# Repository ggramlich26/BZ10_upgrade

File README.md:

# Bezzera BZ10 Upgrade
This Project is a replacement for the original Bezzera BZ10 electronics bringing many new features including the following:
- Temperature regulation for boiler and brewing unit
- Volumetric brewing system based on water flow instead of time only
- Standby functionality
- Automated wake up from standby, so that the machine is heated up already when you get up in the morning
- Display of various temperatures, volume distributed and distribution time
- Preinfusion (time based)
- WIFI: All parameters (temperatures, distribution volume, wake up time, etc.) can be set with a smartphone or computer
- Automated cleaning cycle: Ten cycles of switching distribution on and off for 20 seconds each by pressing only one button

## Building the project
This project is set up to be built with Eclipse Sloeber, which adds Arduino support to the Eclipse IDE. It uses the following Libraries, which can be installed through the library manager:
- TFT_eSPI (Version 1.4.16)
- Time (Version 1.5.0)
- MCP23017 (Version	1.1.2), not Adafruit MCP23017!
- PID (Version 1.2.0)
- ADS115_WE (Version 1.3.6)
- ArduinoJson (Version 6.19.4)
- ESPmDNS
- SPIFFS

Some libraries are also added as source code. If you use the Arduino IDE, please move all files from the libraries/library name/src/ directly into your project directory. If you use Sloeber, you might have to add the library paths in the project settings: Right click your project/Properties/"C/C++ Build"/Settings. In the Tool Settings Tab, expand the compiler and click Include Folders. Add the following paths ```"${workspace_loc:/BZ10_upgrade/libraries/AsyncTCP/src}"``` and ```"${workspace_loc:/BZ10_upgrade/libraries/ESPAsyncWebServer/src}"``` under each of the three compilers.

**Board settings:** You need to [install the ESP32 board for Sloeber](http://wiki.lauerbach.de/wiki/view.do?page=ESP32Entwicklungsumgebungen). Select NodeMCU-32S as board, Upload Protocol: Default, Flash Frequency: 40MHz, Upload Speed: 115200

***Windows:*** Under windows you need to make sure you have make command installed (e.g. through MinGW64: select mingw32-make package). You might also have to [install CP2102 drivers](https://www.silabs.com/developers/usb-to-uart-bridge-vcp-drivers) if you get a timeout error when trying to upload your sketch.

**Before building** 
You will additionally need to modify User_Setup.h in the TFT_eSPI library folder. Uncomment `#define ILI9341_DRIVER` (line 39) and make sure all other lines in this block are commented out. Then search for the uncommented pin definitions and change them to the following:
```C++
#define TFT_DC 		23
#define TFT_CS 		17
#define	TFT_MOSI	32
#define	TFT_SCLK	33
#define	TFT_MISO	14
#define TFT_RST		16
```

## Setting your WiFi credentials
The machine can be configured to connect to your own home WiFi network via the web interface:
 1. Turn the machine off.
 2. Set the brewing switch to manual mode, hold both buttons pressed (This step resets the wifi configuration. You can omit it if you have a fresh setup).
 3. Turn the machine on while holding the buttons pressed. You can release them once the screen is ready.
 4. Wait for 30 seconds
 5. Connect with any device to the WiFi network "BZ10" with no password required.
 6. Open your web browser and type 192.168.4.1 into address bar, hit enter.
 7. Now you will be presented a prompt to enter the new SSID (your WiFi name) and password. You can also set your machines Bonjour name. Finish by hitting the "Set" button.

## Connecting to the machine
You can connect to the machine with a browser on any device. You can use your computer, smartphone or tablet, for example. Please note: The machine currently **only supports http and not https**. If you cannot connect, you might have to change the line ine your browser to http://your-ip. There are multiple ways to connect:
### Access point mode
When the machine cannot establish a connection to a wifi network, it automatically creates a hotspot after 30 seconds. Simply connect to the network BZ10 with your device. In the browser type in 192.168.4.1 to go to your machine and change the settings.
### Local WiFi
If the machine is connected to your local WiFi network (little wifi icon shown in the bottom), you can reach it by typing its IP in your browser (use your router configuration website to find out what that is and to make it always the same). Alternatively, you can find it with Bonjour. This works out of the box on Apple and Linux machines and requires an extra [installation from the apple resources](https://support.apple.com/downloads/bonjour-for-windows) on windows. You can then reach the machine by typing bz10.local into your browser. If you want to change the address to something else than bz10, you can modify the Bonjour name on the machine website.
## Usage
Your new espresso machine has a lot more functions than before. This is how you can use them
- **Standard manual distribution:** Flip your distribution switch in the manual distribution position for manual dosing and cooling flush
- **True volumetric distribution:** Flip your distribution switch in the volumetric distribution position for automatic dosing. You can set the desired volume via the website. You will also need to set an offset volume that compensates for the water being moved into the brewing unit but not going through your coffee powder. The best way to do so is to measure the difference between set and actual distribution volume and entering this value via Blynk.
- **Preinfusion:** If you set a preinfusion buildup and wait time on the website, volumetric distribution will come with a preinfusion. This is achieved by turning on the pump for the preinfusion buildup time and then waiting for the preinfusion wait time before starting the actual extraction.
- **Cooling flush:** Since the BZ10 is a HX machine, you will still need to perform a cooling flush just like before the upgrade. But in order to make this process more repeatable, you get a timer showing the time passed after your cooling flush. In order to get this functionality, short press the right button before starting your cooling flush. You will see, that the timer starts counting up once you finished your cooling flush.
- **Standby:** Press the left button shortly to enter standby mode. You can also define a period of time after which the machine will automatically enter standby if it has not been used via Blynk.
- **Automated wake up from standby:** Tired of having to wait for half an hour after getting up until you can finally brew your coffee? Just turn your espresso machine on and press the standby button before going to bed. Now you can set a wake up time via the website. If you set it to half an hour before your alarm goes off, your machine will be all ready for your coffee first thing in the morning. This feature only works if wifi is enabled and the machine has connection to the internet, since it needs to get the current time from a remote server.
- **Automated cleaning cycle:** Cleaning is boring and time consuming task. But now you can save a lot of time. Pressing the right button for 3s or more will start an automated cleaning cycle: Your machine will build up pressure for 20s and then release it for another 20s. This process is repeated 10 times.
- **Disable WiFi:** You got everything set up and don't want your machine to be in the internet any more? Nothing easier than that. Just press the left button for 3s or longer. Now you can see the wifi symbol disappearing from the display and once you restart your machine it won't even connect to your WiFi network any more. To enable WiFi again, just press the left button for 3s or longer again. 
- **Display:** Pretty obvious but you now have a display showing various temperatures, the volume distributed and the time your distribution took (preinfusion time not included). The red circle shows the boiler temperature, the orange circle on the right shows the brewing head temperature and the blue circle in the top shows one additional temperature. I attached this sensor to the tube leading from the heat exchanger to the brewing head.

## Code overview
The machine functionality is based on state machines. There are two state machines for boiler and brewing unit temperature control. Another state machine controls the brewing cycle, one is used for the display, and a last one is responsible for the overall machine state including standby functionality. All state machines are visually shown under `/State machines/State machines.odg`. 
In order to make the program more flexible for other hardware, a hardware abstraction class has been written (`dev.c`). Adapting this class will allow the project to run on a different hardware as well.
Besides machine logic, a faster library for TSIC temperature sensors has been developed.
### Brewing state machine
### Boiler heater state machine
### Brewing unit heater state machine
### Display state machine
### Machine status state machine

## The Hardware
There are eagle layout and gerber files available for a PCB designed with this project. You can simply send those files to a manufacturer such as JLCPCB or Seeedstudio. At the moment I also have a few available from my order, that I could have sent to you for very little money. In case you have trouble soldering SMD (surface mounted device) components, we could also discuss having an assembled PCB shipped to you.
### Hardware on the PCB
You will need all need the components listed below to complete the PCB. All of them can be bought from standard suppliers, including Reichelt, Farnell, Mouser etc.

**Resistors:**
|Value|Package | Quantity | Link |
|--|--|--|--
|2.2k|0603|1
|4.7k|0603|2
|10k|0603|2
|22k|0603|3
|47k|0603|2
|100k|0603|1
220k|0603|2
330k|0603|3
1M|0603|1
4.7M|0603|1

**Capacitors:**
|Value|Package | Quantity | Link |
|--|--|--|--
2.2n|0603|1
10n|0603|2
22n|0603|1
100n|0603|2

**Semiconductors:**
|Name|Package | Quantity | Link |
|--|--|--|--
| **Transistors**|
 IRLML5203|MICRO3|1|[farnell](https://de.farnell.com/infineon/irlml5203trpbf/mosfet-p-kanal-30v-3a-sot23/dp/9103511?st=irlml5203)
 BSS138BK|SOT-23|6|[farnell](https://de.farnell.com/nexperia/bss138bk-215/mosfet-n-kanal-60v-0-36a-sot23/dp/2053833?st=bss138bk)
 **Diodes**|
 BAS21|SOT-23|2|[farnell](https://de.farnell.com/diodes-inc/bas21/schaltdiode-250v-0-25w-sot23-3/dp/1902406?st=bas21)
 **ICs**|
 MCP23017SO|SO28W|1|[farnell](https://de.farnell.com/microchip/mcp23017-e-so/16bit-expander-i-o-i2c-i-f-smd/dp/1332087?st=mcp23017)
 NE555D|SO-8|1|[farnell](https://de.farnell.com/texas-instruments/ne555d/precision-timers-linear/dp/3121191?st=ne555d)
 MCP6002-E/SN|SOIC-8|1|[farnell](https://de.farnell.com/microchip/mcp6002-e-sn/op-verst-rker-1mhz-0-6v-us-4500uv/dp/1332118?st=mcp6002-e/sn)
  ADS1115|MSOP10|1|[e.g. from far east](https://www.aliexpress.com/item/32809831068.html?spm=a2g0s.9042311.0.0.27424c4daHnzqu)

**Boards:**
|Name|Package | Quantity | Link |
|--|--|--|--
| ESP32 nodeMCU with external antenna||1|[from far east](https://www.aliexpress.com/item/4000155919030.html?spm=a2g0s.9042311.0.0.27424c4d4ySog2)|

**Power supply:**
|Name|Package | Quantity | Link |
|--|--|--|--
| HLK-PM01 (5V power supply)||1|[from far east](https://www.aliexpress.com/item/4000534910455.html?spm=a2g0s.9042311.0.0.2f024c4dAwDw9T)|

**Connectors:**
|Name|rows|positions|m/f| Quantity | Comment |
|--|--|--|--|--|--
pinheader 2.54mm|1|2|f+m|4|boiler SSR, boiler probe, NTC, tank switch
pinheader 2.54mm|1|3|f+m|5|connecting TSIC temperature and flow sensors
pinheader 2.54mm|1|6|f+m|2|connecting arduino SSR board
pinheader 2.54mm|1|8|f+m|2|connecting switches and LEDs
pinheader 2.54mm|1|9|f+m|2|display
wire to board connectors, RM5 with screws|1|2|f|1|230V connector [farnell](https://de.farnell.com/camdenboss/ctb1500-2/terminal-block-5mm-2-way/dp/3377326?st=wire%20to%20board%20rm5)

### Hardware off the PCB in the machine
- Arduino SSR board with 4 SSRs (e.g. [Arduino SSR module on Amazon](https://www.amazon.de/Ecloud-4-Channel-Trigger-SSR-Modul-Brett-Arduino-resistivem/dp/B01E6KUMTI/ref=sr_1_4?__mk_de_DE=%C3%85M%C3%85%C5%BD%C3%95%C3%91&dchild=1&keywords=arduino%20ssr%204&qid=1605773053&quartzVehicle=812-409&replacementKeywords=arduino%20ssr&sr=8-4))
- One SSRs for 230V, switchable by 3-5VDC (called SSR-40 DA) for boiler heater and electric brewing unit heater (e.g. [SSR on Amazon](https://www.amazon.de/KKmoon-24V-380V-SSR-40-Relaismodul-Temperaturregler/dp/B010Q6898C/ref=sr_1_3?__mk_de_DE=%C3%85M%C3%85%C5%BD%C3%95%C3%91&dchild=1&keywords=ssr&qid=1605773227&sr=8-3))
- SPI TFT Display 320x240 Pixels with ILI9341 (e.g. [Display on Amazon](https://www.amazon.de/gp/product/B01E0MGZU2/ref=ppx_yo_dt_b_asin_title_o09_s00?ie=UTF8&psc=1))
- Alternative switches: Brewing switch should be replaced by a 3 fixed positions switch, indicator lights should be replaced by push buttons with LEDs, so that they can serve as indicator lights and inputs at the same time. (I used [those](https://www.aliexpress.com/item/4000454624299.html?spm=a2g0s.9042311.0.0.27424c4dZZ9bgU) instead of the indicator lights (3-6V, momentary version) and [those](https://www.aliexpress.com/item/4000028451024.html?spm=a2g0s.9042311.0.0.27424c4dZZ9bgU) for the original two push buttons (5V, latching fixation, blue LED, 2 positions for on/off, 3 positions for brewing switch). If you want to use those switches for on/off, you will need to add a relay in the power supply chain because they are not strong enough for the entire espresso machine power!
- TSIC 306 temperature sensors, 3 pieces
- Flow sensors, 2 pieces (e.g. [from far east](https://www.aliexpress.com/item/32949504762.html?spm=a2g0o.productlist.0.0.4ce346a5MgsR2I&algo_pvid=a8a64f8f-1437-4fca-a7c7-6e23d0d647a1&algo_expid=a8a64f8f-1437-4fca-a7c7-6e23d0d647a1-28&btsid=2100bdf016057823158403471e2893&ws_ab_test=searchweb0_0,searchweb201602_,searchweb201603_))
- Quite some wiring. I chose Oelflex Heat for its heat resistance up to 180°C (purchased from Conrad electronics)

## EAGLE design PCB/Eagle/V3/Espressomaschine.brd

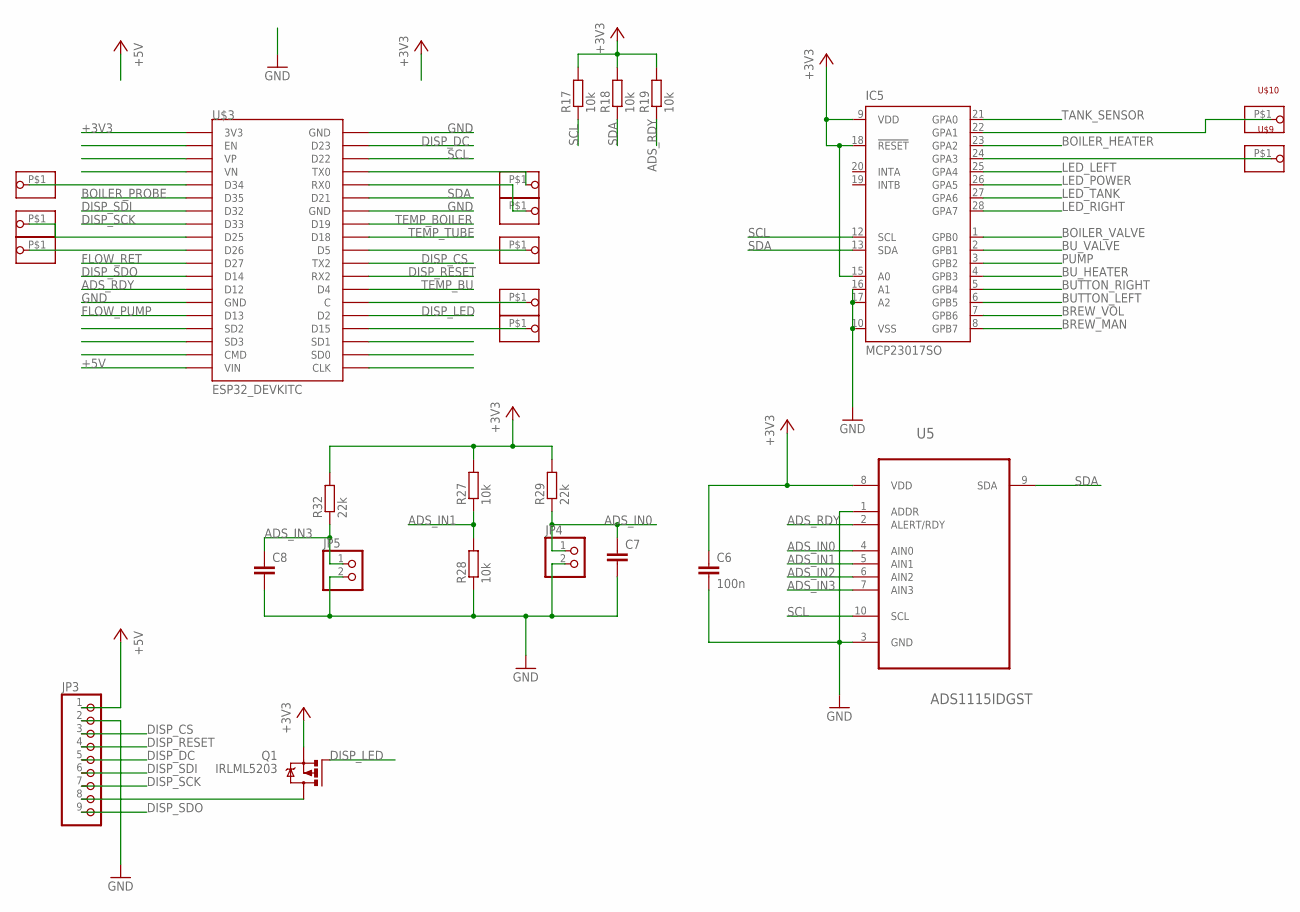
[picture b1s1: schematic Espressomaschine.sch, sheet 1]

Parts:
C6: 100n; C0603
C7, C8: C-EUC0603; C0603
IC5: MCP23017SO; SO28W
JP3: PINHD-1X9; 1X09
JP4, JP5: PINHD-1X2; 1X02
Q1: IRLML5203; MICRO3
R17, R18, R19, R27, R28: 10k; R0603
R29, R32: 22k; R0603
U5: ADS1115IDGST; SOP50P490X110-10N
U$3: ESP32_DEVKITC
U$5, U$6, U$7, U$8, U$9, U$10, U$11, U$12, U$13, U$14: PINHD-1X1SMD_RM1.27; 1X01_SMD_RM1.27

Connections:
+3V3: C6.1, IC5.9 (VDD), IC5.15 (A0), IC5.18 (!RESET), Q1.2 (S), R17.2, R18.2, R19.2, R27.2, R29.2, R32.2, U5.8 (VDD), U$3.3V3; also elsewhere on the board
+5V: JP3.1, U$3.VIN; also elsewhere on the board
ADS_IN0: C7.1, JP4.1, R29.1, U5.4 (AIN0)
ADS_IN1: R27.1, R28.2, U5.5 (AIN1)
ADS_IN2: U5.6 (AIN2); also elsewhere on the board
ADS_IN3: C8.1, JP5.1, R32.1, U5.7 (AIN3)
ADS_RDY: R19.1, U5.2 (ALERT/RDY), U$3.D12
BOILER_HEATER: IC5.23 (GPA2); also elsewhere on the board
BOILER_PROBE: U$3.D35; also elsewhere on the board
BOILER_VALVE: IC5.1 (GPB0); also elsewhere on the board
BREW_MAN: IC5.8 (GPB7); also elsewhere on the board
BREW_VOL: IC5.7 (GPB6); also elsewhere on the board
BUTTON_LEFT: IC5.6 (GPB5); also elsewhere on the board
BUTTON_RIGHT: IC5.5 (GPB4); also elsewhere on the board
BU_HEATER: IC5.4 (GPB3); also elsewhere on the board
BU_VALVE: IC5.2 (GPB1); also elsewhere on the board
DISP_CS: JP3.3, U$3.TX2
DISP_DC: JP3.5, U$3.D23
DISP_LED: Q1.1 (G), U$3.D2
DISP_RESET: JP3.4, U$3.RX2
DISP_SCK: JP3.7, U$3.D33
DISP_SDI: JP3.6, U$3.D32
DISP_SDO: JP3.9, U$3.D14
FLOW_PUMP: U$3.D13; also elsewhere on the board
FLOW_RET: U$3.D27; also elsewhere on the board
GND: C6.2, C7.2, C8.2, IC5.10 (VSS), IC5.16 (A1), IC5.17 (A2), JP3.2, JP4.2, JP5.2, R28.1, U5.1 (ADDR), U5.3 (GND), U$3.GND@1 (GND), U$3.GND@2 (GND), U$3.GND@3 (GND); also elsewhere on the board
LED_LEFT: IC5.25 (GPA4); also elsewhere on the board
LED_POWER: IC5.26 (GPA5); also elsewhere on the board
LED_RIGHT: IC5.28 (GPA7); also elsewhere on the board
LED_TANK: IC5.27 (GPA6); also elsewhere on the board
unnamed: U$3.C, U$7.P$1
unnamed: IC5.22 (GPA1), U$10.P$1
unnamed: IC5.24 (GPA3), U$9.P$1
unnamed: U$3.TX0, U$5.P$1
unnamed: JP3.8, Q1.3 (D)
unnamed: U$3.RX0, U$11.P$1
unnamed: U$3.D5, U$6.P$1
unnamed: U$3.D15, U$8.P$1
unnamed: U$3.D34, U$12.P$1
unnamed: U$3.D25, U$13.P$1
unnamed: U$3.D26, U$14.P$1
PUMP: IC5.3 (GPB2); also elsewhere on the board
SCL: IC5.12 (SCL), R17.1, U5.10 (SCL), U$3.D22
SDA: IC5.13 (SDA), R18.1, U5.9 (SDA), U$3.D21
TANK_SENSOR: IC5.21 (GPA0); also elsewhere on the board
TEMP_BOILER: U$3.D19; also elsewhere on the board
TEMP_BU: U$3.D4; also elsewhere on the board
TEMP_TUBE: U$3.D18; also elsewhere on the board

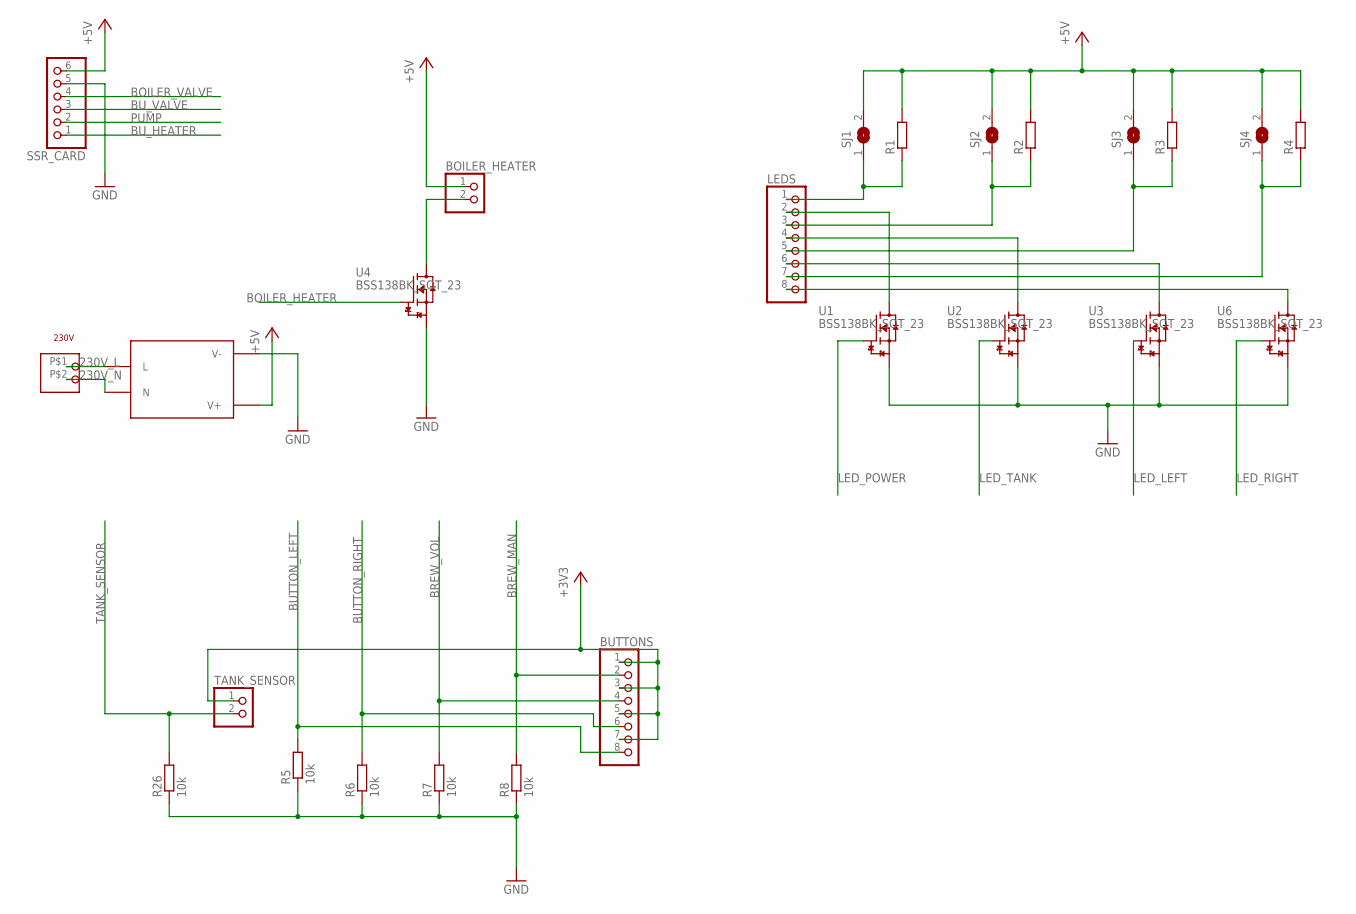
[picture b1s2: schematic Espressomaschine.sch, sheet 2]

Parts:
230V: 1X2RM5; 1X02_RM5
BOILER_HEATER: PINHD-1X2; 1X02
BUTTONS: PINHD-1X8; 1X08
LEDS: PINHD-1X8; 1X08
R1, R2, R3, R4: R-EU_R0603; R0603
R5, R6, R7, R8, R26: 10k; R0603
SJ1, SJ2, SJ3, SJ4: SJ
SSR_CARD: PINHD-1X6; 1X06
TANK_SENSOR: PINHD-1X2; 1X02
U1, U2, U3, U4, U6: BSS138BK_SOT_23; SOT23
U$1: HLK-PM0X

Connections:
230V_L: 230V.P$1 (1), U$1.L
230V_N: 230V.P$2 (2), U$1.N
+3V3: BUTTONS.1, BUTTONS.3, BUTTONS.5, BUTTONS.7, TANK_SENSOR.1; also elsewhere on the board
+5V: BOILER_HEATER.1, R1.2, R2.2, R3.2, R4.2, SJ1.2, SJ2.2, SJ3.2, SJ4.2, SSR_CARD.6, U$1.V+; also elsewhere on the board
BOILER_HEATER: U4.1 (G); also elsewhere on the board
BOILER_VALVE: SSR_CARD.4; also elsewhere on the board
BREW_MAN: BUTTONS.2, R8.2; also elsewhere on the board
BREW_VOL: BUTTONS.4, R7.2; also elsewhere on the board
BUTTON_LEFT: BUTTONS.8, R5.2; also elsewhere on the board
BUTTON_RIGHT: BUTTONS.6, R6.2; also elsewhere on the board
BU_HEATER: SSR_CARD.1; also elsewhere on the board
BU_VALVE: SSR_CARD.3; also elsewhere on the board
GND: R5.1, R6.1, R7.1, R8.1, R26.1, SSR_CARD.5, U1.2 (S), U2.2 (S), U3.2 (S), U4.2 (S), U6.2 (S), U$1.V-; also elsewhere on the board
LED_LEFT: U3.1 (G); also elsewhere on the board
LED_POWER: U1.1 (G); also elsewhere on the board
LED_RIGHT: U6.1 (G); also elsewhere on the board
LED_TANK: U2.1 (G); also elsewhere on the board
unnamed: LEDS.1, R1.1, SJ1.1
unnamed: LEDS.3, R2.1, SJ2.1
unnamed: LEDS.5, R3.1, SJ3.1
unnamed: LEDS.8, U6.3 (D)
unnamed: LEDS.6, U3.3 (D)
unnamed: BOILER_HEATER.2, U4.3 (D)
unnamed: LEDS.7, R4.1, SJ4.1
unnamed: LEDS.4, U2.3 (D)
unnamed: LEDS.2, U1.3 (D)
PUMP: SSR_CARD.2; also elsewhere on the board
TANK_SENSOR: R26.2, TANK_SENSOR.2; also elsewhere on the board

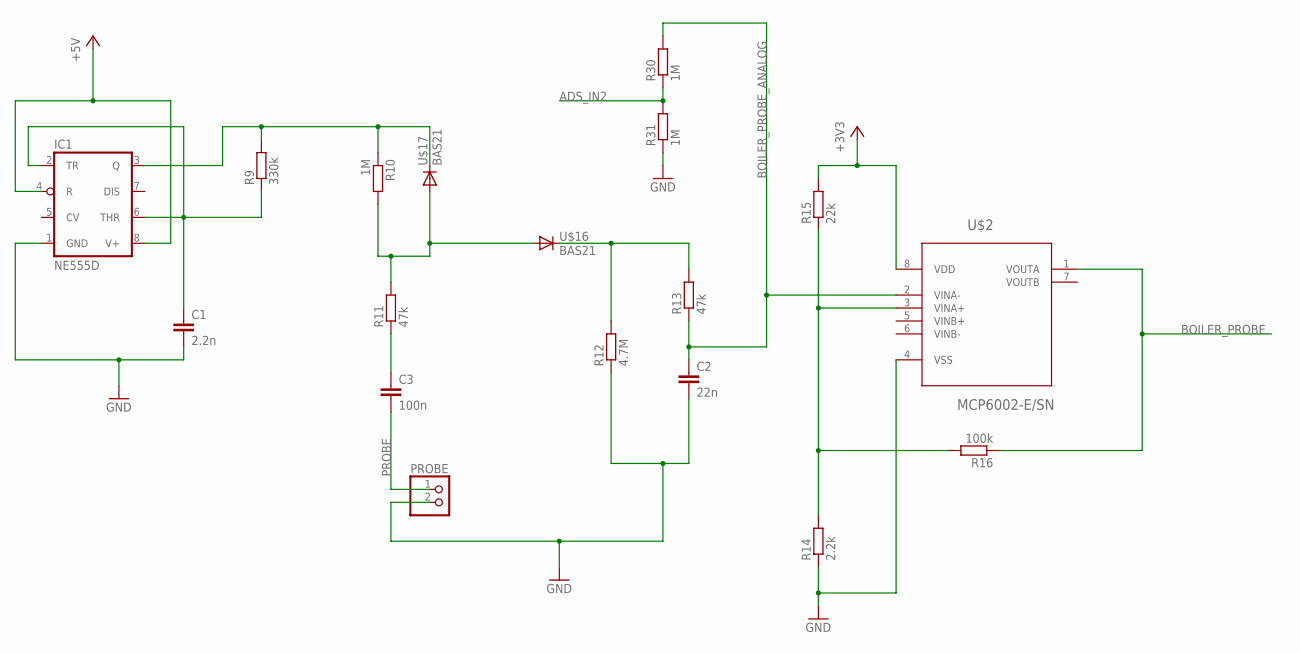
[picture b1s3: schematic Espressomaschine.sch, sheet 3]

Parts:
C1: 2.2n; C0603
C2: 22n; C0603
C3: 100n; C0603
IC1: NE555D; SO08
PROBE: PINHD-1X2; 1X02
R9: 330k; R0603
R10, R30, R31: 1M; R0603
R11, R13: 47k; R0603
R12: 4.7M; R0603
R14: 2.2k; R0603
R15: 22k; R0603
R16: 100k; R0603
U$2: MCP6002-E/SN; SOIC127P600X175-8N
U$16, U$17: BAS21; SOT23

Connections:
+3V3: R15.2, U$2.8 (VDD); also elsewhere on the board
+5V: IC1.4 (R), IC1.8 (V+); also elsewhere on the board
ADS_IN2: R30.1, R31.2; also elsewhere on the board
BOILER_PROBE: R16.1, U$2.1 (VOUTA); also elsewhere on the board
BOILER_PROBE_ANALOG: C2.1, R13.1, R30.2, U$2.2 (VINA-)
GND: C1.2, C2.2, IC1.1 (GND), PROBE.2, R12.1, R14.1, R31.1, U$2.4 (VSS); also elsewhere on the board
unnamed: C1.1, IC1.2 (TR), IC1.6 (THR), R9.1
unnamed: R10.2, R11.2, U$16.1 (A), U$17.1 (A)
unnamed: C3.1, R11.1
unnamed: IC1.3 (Q), R9.2, R10.1, U$17.3 (C)
unnamed: R12.2, R13.2, U$16.3 (C)
unnamed: R14.2, R15.1, R16.2, U$2.3 (VINA+)
PROBE: C3.2, PROBE.1

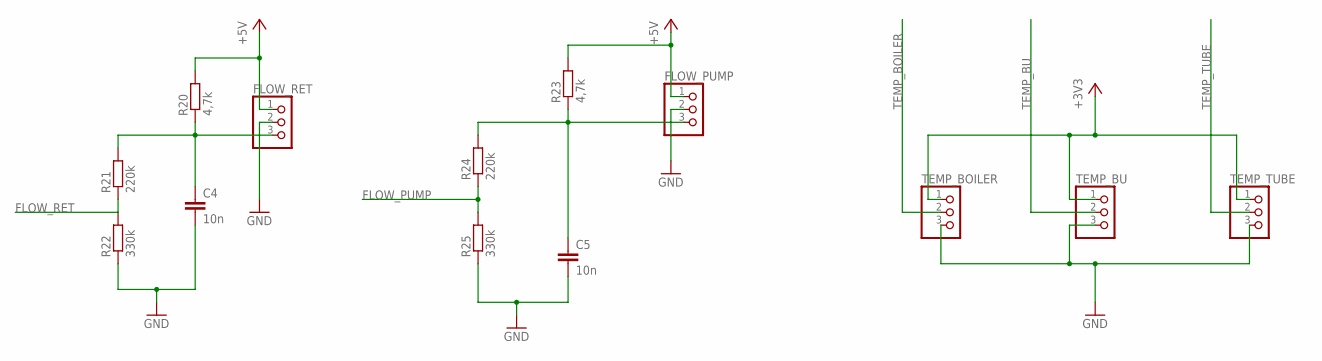
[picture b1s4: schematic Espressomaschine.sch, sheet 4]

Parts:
C4, C5: 10n; C0603
FLOW_PUMP: PINHD-1X3; 1X03
FLOW_RET: PINHD-1X3; 1X03
R20, R23: 4,7k; R0603
R21, R24: 220k; R0603
R22, R25: 330k; R0603
TEMP_BOILER: PINHD-1X3; 1X03
TEMP_BU: PINHD-1X3; 1X03
TEMP_TUBE: PINHD-1X3; 1X03

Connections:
+3V3: TEMP_BOILER.1, TEMP_BU.1, TEMP_TUBE.1; also elsewhere on the board
+5V: FLOW_PUMP.1, FLOW_RET.1, R20.2, R23.2; also elsewhere on the board
FLOW_PUMP: R24.1, R25.2; also elsewhere on the board
FLOW_RET: R21.1, R22.2; also elsewhere on the board
GND: C4.2, C5.2, FLOW_PUMP.2, FLOW_RET.2, R22.1, R25.1, TEMP_BOILER.3, TEMP_BU.3, TEMP_TUBE.3; also elsewhere on the board
unnamed: C4.1, FLOW_RET.3, R20.1, R21.2
unnamed: C5.1, FLOW_PUMP.3, R23.1, R24.2
TEMP_BOILER: TEMP_BOILER.2; also elsewhere on the board
TEMP_BU: TEMP_BU.2; also elsewhere on the board
TEMP_TUBE: TEMP_TUBE.2; also elsewhere on the board

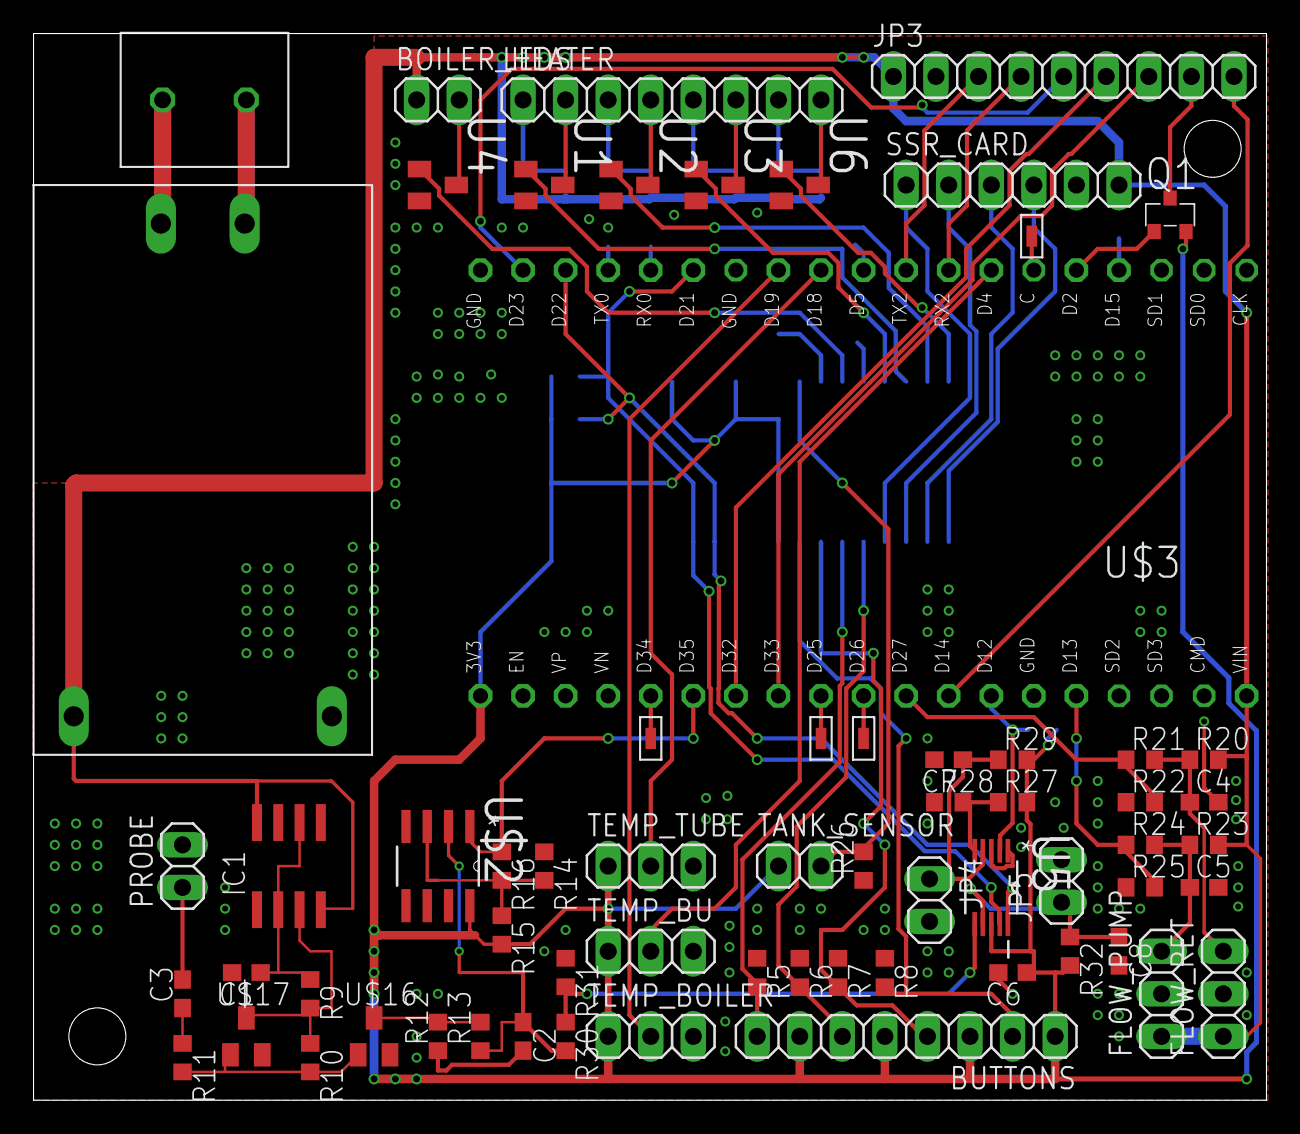
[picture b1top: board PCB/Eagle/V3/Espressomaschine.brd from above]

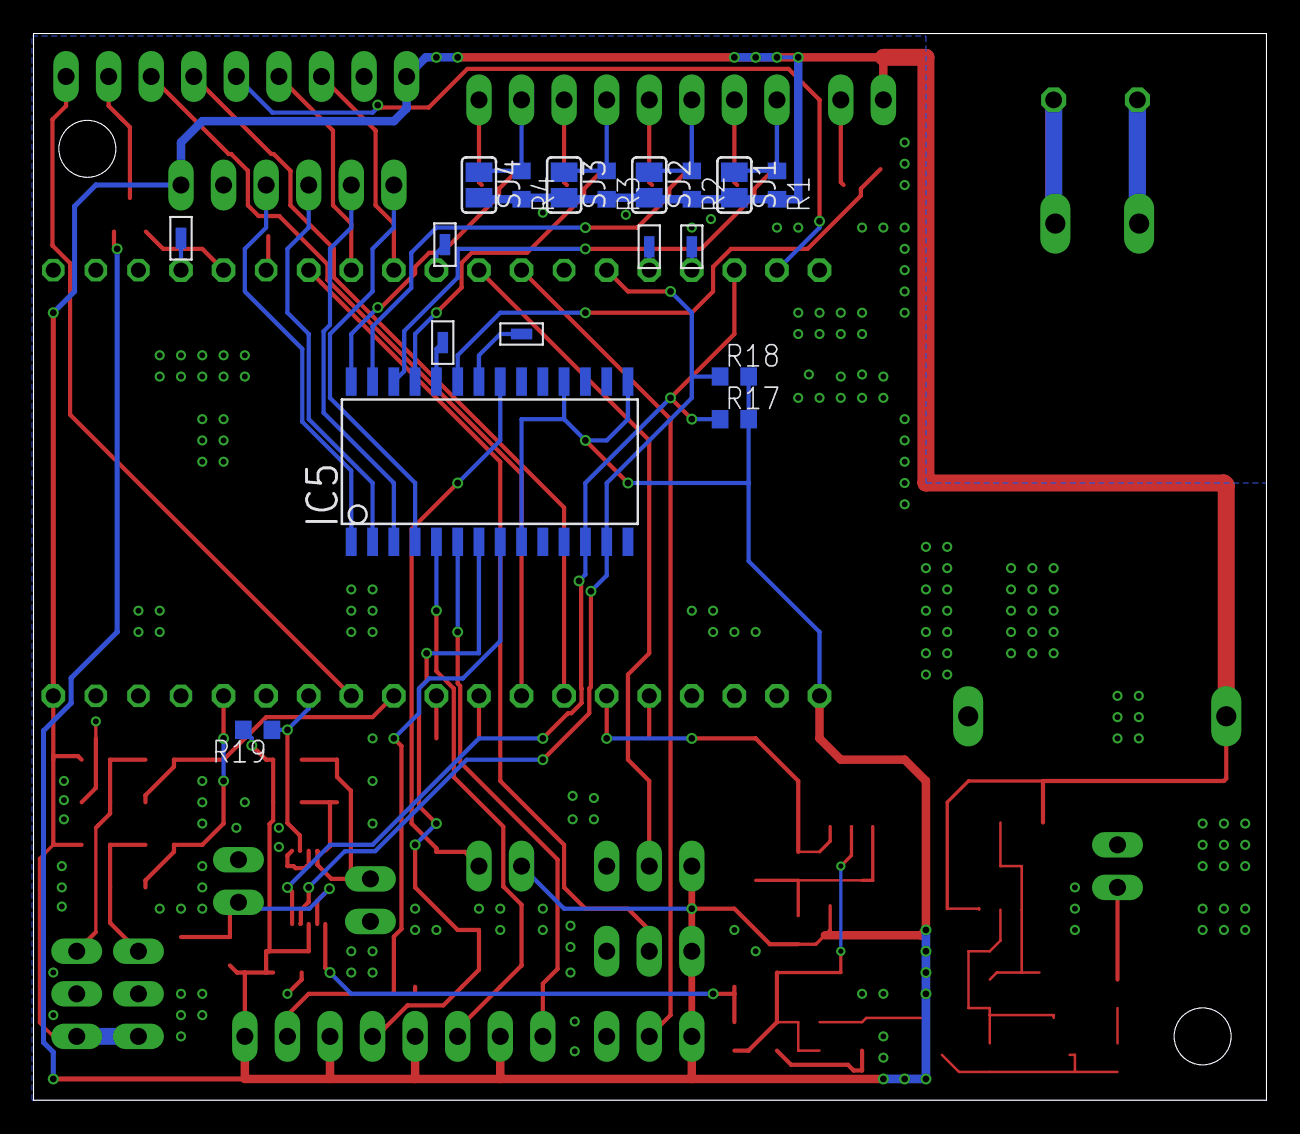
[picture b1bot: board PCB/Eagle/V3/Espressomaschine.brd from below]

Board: 2 copper layers, 73.6 x 63.6 mm, 83 parts (18 on the bottom side), 69 nets.
